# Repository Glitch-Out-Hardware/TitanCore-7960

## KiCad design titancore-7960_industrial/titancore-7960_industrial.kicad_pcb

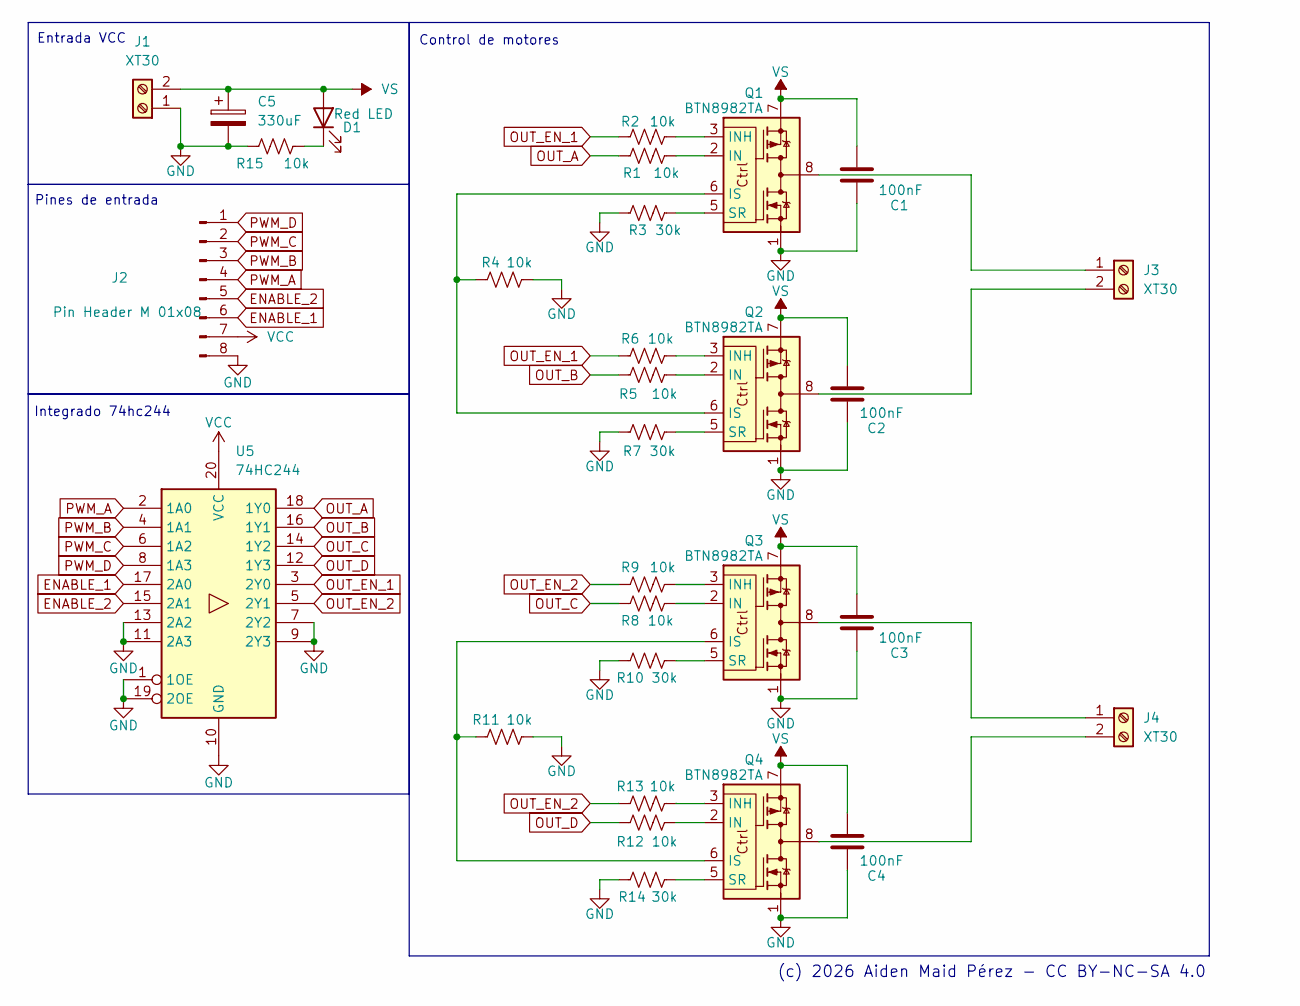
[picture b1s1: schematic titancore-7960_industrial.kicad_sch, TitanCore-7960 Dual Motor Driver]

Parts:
C1, C2, C3, C4: 100nF; C_0805_2012Metric_Pad1.18x1.45mm_HandSolder
C5: 330uF; CP_Radial_Tantal_D9.0mm_P5.00mm
D1: Red LED; LED_0805_2012Metric
J1, J3, J4: XT30; AMASS_XT30U-F_1x02_P5.0mm_Vertical
J2: Pin Header M 01x08; PinHeader_1x08_P2.54mm_Vertical
Q1, Q2, Q3, Q4: BTN8982TA; TO-263-7_TabPin8
R1, R2, R4, R5, R6, R8, R9, R11, R12, R13, R15: 10k; R_0805_2012Metric_Pad1.20x1.40mm_HandSolder
R3, R7, R10, R14: 30k; R_0805_2012Metric_Pad1.20x1.40mm_HandSolder
U5: 74HC244; SOIC127P1032X265-20N

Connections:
ENABLE_1: J2.6, U5.17 (2A0)
ENABLE_2: J2.5, U5.15 (2A1)
GND: C1.2, C2.2, C3.2, C4.2, C5.2, J1.1, J2.8, Q1.1, Q2.1, Q3.1, Q4.1, R3.2, R4.1, R7.2, R10.2, R11.1, R14.2, R15.2, U5.1 (1OE), U5.7 (2Y2), U5.9 (2Y3), U5.10 (GND), U5.11 (2A3), U5.13 (2A2), U5.19 (2OE)
unnamed: D1.1 (K), R15.1
unnamed: J3.1, Q1.4, Q1.8
unnamed: J3.2, Q2.4, Q2.8
unnamed: J4.1, Q3.4, Q3.8
unnamed: J4.2, Q4.4, Q4.8
unnamed: Q1.2 (IN), R1.1
unnamed: Q1.3 (INH), R2.1
unnamed: Q1.6 (IS), Q2.6 (IS), R4.2
unnamed: Q1.5 (SR), R3.1
unnamed: Q2.2 (IN), R5.1
unnamed: Q2.3 (INH), R6.1
unnamed: Q2.5 (SR), R7.1
unnamed: Q3.2 (IN), R8.1
unnamed: Q3.3 (INH), R9.1
unnamed: Q3.6 (IS), Q4.6 (IS), R11.2
unnamed: Q3.5 (SR), R10.1
unnamed: Q4.2 (IN), R12.1
unnamed: Q4.3 (INH), R13.1
unnamed: Q4.5 (SR), R14.1
OUT_A: R1.2, U5.18 (1Y0)
OUT_B: R5.2, U5.16 (1Y1)
OUT_C: R8.2, U5.14 (1Y2)
OUT_D: R12.2, U5.12 (1Y3)
OUT_EN_1: R2.2, R6.2, U5.3 (2Y0)
OUT_EN_2: R9.2, R13.2, U5.5 (2Y1)
PWM_A: J2.4, U5.2 (1A0)
PWM_B: J2.3, U5.4 (1A1)
PWM_C: J2.2, U5.6 (1A2)
PWM_D: J2.1, U5.8 (1A3)
VCC: J2.7, U5.20 (VCC)
VS: C1.1, C2.1, C3.1, C4.1, C5.1, D1.2 (A), J1.2, Q1.7, Q2.7, Q3.7, Q4.7

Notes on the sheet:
Entrada VCC
Pines de entrada
Integrado 74hc244
Control de motores
(c) 2026 Aiden Maid Pérez - CC BY-NC-SA 4.0

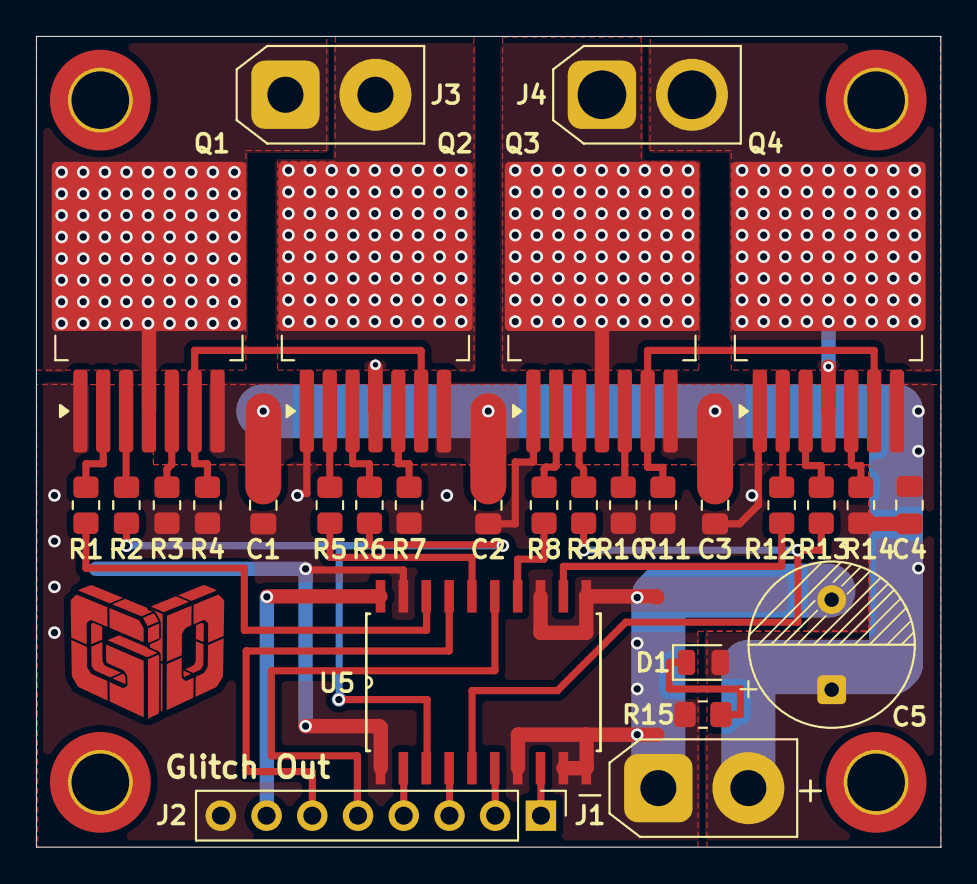
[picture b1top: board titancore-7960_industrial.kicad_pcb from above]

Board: 2 copper layers, 50.3 x 45.0 mm, 30 parts (0 on the bottom side), 34 nets.

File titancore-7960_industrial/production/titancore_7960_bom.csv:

Designator,Footprint,Quantity,Value,LCSC Part #
"C1, C2, C3, C4",0805,4,100nF,
C5,CP_Radial_Tantal_D9.0mm_P5.00mm,1,330uF,
D1,0805,1,Red LED,
"J1, J3, J4",AMASS_XT30U-F_1x02_P5.0mm_Vertical,3,XT30,
J2,PinHeader_1x08_P2.54mm_Vertical,1,Pin Header M 01x08,
"Q1, Q2, Q3, Q4",TO-263-7_TabPin8,4,BTN8982TA,
"R1, R11, R12, R13, R15, R2, R4, R5, R6, R8, R9",0805,11,10k,
"R10, R14, R3, R7",0805,4,30k,
U5,SOIC127P1032X265-20N,1,74HC244,

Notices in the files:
titancore-7960_industrial/titancore-7960_industrial.kicad_sch:
Licensed under CC BY-NC-SA 4.0
